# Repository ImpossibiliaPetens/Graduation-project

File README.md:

# Graduation-project

毕业设计项目的硬件资料与申报材料。

## 项目列表

| 目录 | 说明 | 状态 |
|---|---|---|
| [`hardware/stm32-environment-monitor`](hardware/stm32-environment-monitor) | **基于 STM32 的多功能环境智能监控系统**：温湿度、光照、RTC、OLED、按键、LED、蜂鸣器、12V 灯带控制，12V 输入板载降压 | V1.2，已提交嘉立创打样 |
| [`hardware/garden-watering-system`](hardware/garden-watering-system) | **智能花园浇水系统**：STM32F103C8T6 开发板 + BH1750 光照 + SHT30 温湿度 + 土壤湿度 + OLED + 4 按键，白天且土壤干才浇水（水泵/电磁阀用 LED 模拟），嘉立创 EDA 工程、Gerber、BOM、物资清单 | 硬件完成，已生成打板数据；程序待写 |
| [`hardware/parking-bluepill`](hardware/parking-bluepill) | **4 车位检测板**：Blue Pill 核心板 + 4 个红外反射传感器 + OLED（KiCad 工程） | `main` 为初版；**更新版在分支 [`claude/blissful-cannon-at318t`](../../tree/claude/blissful-cannon-at318t)**（尚未合并） |
| [`smart-agriculture`](smart-agriculture) | **禾智云枢：多模态 AI 视觉 + 农业智能体的智慧农业大棚沙盘**（800×400mm，STM32F4 + 4G/MQTT/OneNET）：创新创业训练计划申报书、问题—对策图、系统原理图、搭建工程蓝图、三维展示 | 方案设计阶段 |

## 环境监控板（V1.2）简介

- 主控：立创·地阔星 STM32F103C8T6 开发板，插在 2×20 排母上。
- 传感与显示：GXHT30C 温湿度、SD3077 实时时钟（CR1220 备份电池）、0.96" OLED（4P 母座）、光敏电阻。
- 输出：有源蜂鸣器、红/绿/黄 LED、12V LED 灯带（AO3400A 开关）。
- 输入：4 个按键（PA0~PA3）。
- 供电：12V DC 座 → 保险丝 → XL1509 降压到 5V；3.3V 由开发板 LDO 提供。
- 下载程序：开发板自带 SWD 口，接 DAP-Link；Type-C 只供电。

更多内容（引脚表、BOM、Gerber、装配注意事项）见
[环境监控板 README](hardware/stm32-environment-monitor/README.md)，
原理图见 [`docs/原理图.png`](hardware/stm32-environment-monitor/docs/原理图.png)。

## 车位检测板的更新版

更新版（2026-11-12）在分支 `claude/blissful-cannon-at318t`，`main` 上还是旧版。主要改动：

- 核心板改为 GD32F103C8T6 Type-C 核心板（引脚与 Blue Pill 兼容）。
- 传感器由 VCNT2030 改为 XL-ITR8307（成兴光，现货，引脚外露好焊）。
- 修正 OLED 引脚顺序，加去耦电容和 GND 铺铜，附嘉立创 SMT 的 BOM。
- PCB 文件改为 KiCad 9 格式，方便导入嘉立创 EDA。

详细说明见该分支的 `hardware/parking-bluepill/CHANGES.md`。

## 禾智云枢（智慧农业）简介

- 痛点：整体方案成本高、单点设备数据孤立、长势靠人工巡检、交互门槛高、AI 直控不安全、实训缺载体。
- 方案：STM32F4 + EC800K 4G/MQTT + OneNET 底座；AgriLeaf-Det / AgriGrow-Seg / AgriFusion / AgriAgent 四个 AI 模块；“建议—审批—执行”分级控制，断网时本地规则兜底。
- 材料：[申报书](smart-agriculture/项目申报书_公开版.docx)、[商业计划书](smart-agriculture/商业计划书.docx)；详见 [smart-agriculture/README.md](smart-agriculture/README.md)。

## 工具

- 环境监控板：嘉立创 EDA 专业版（`.epro`）
- 车位检测板：KiCad
- 智慧农业沙盘：STM32CubeMX、OneNET 云平台

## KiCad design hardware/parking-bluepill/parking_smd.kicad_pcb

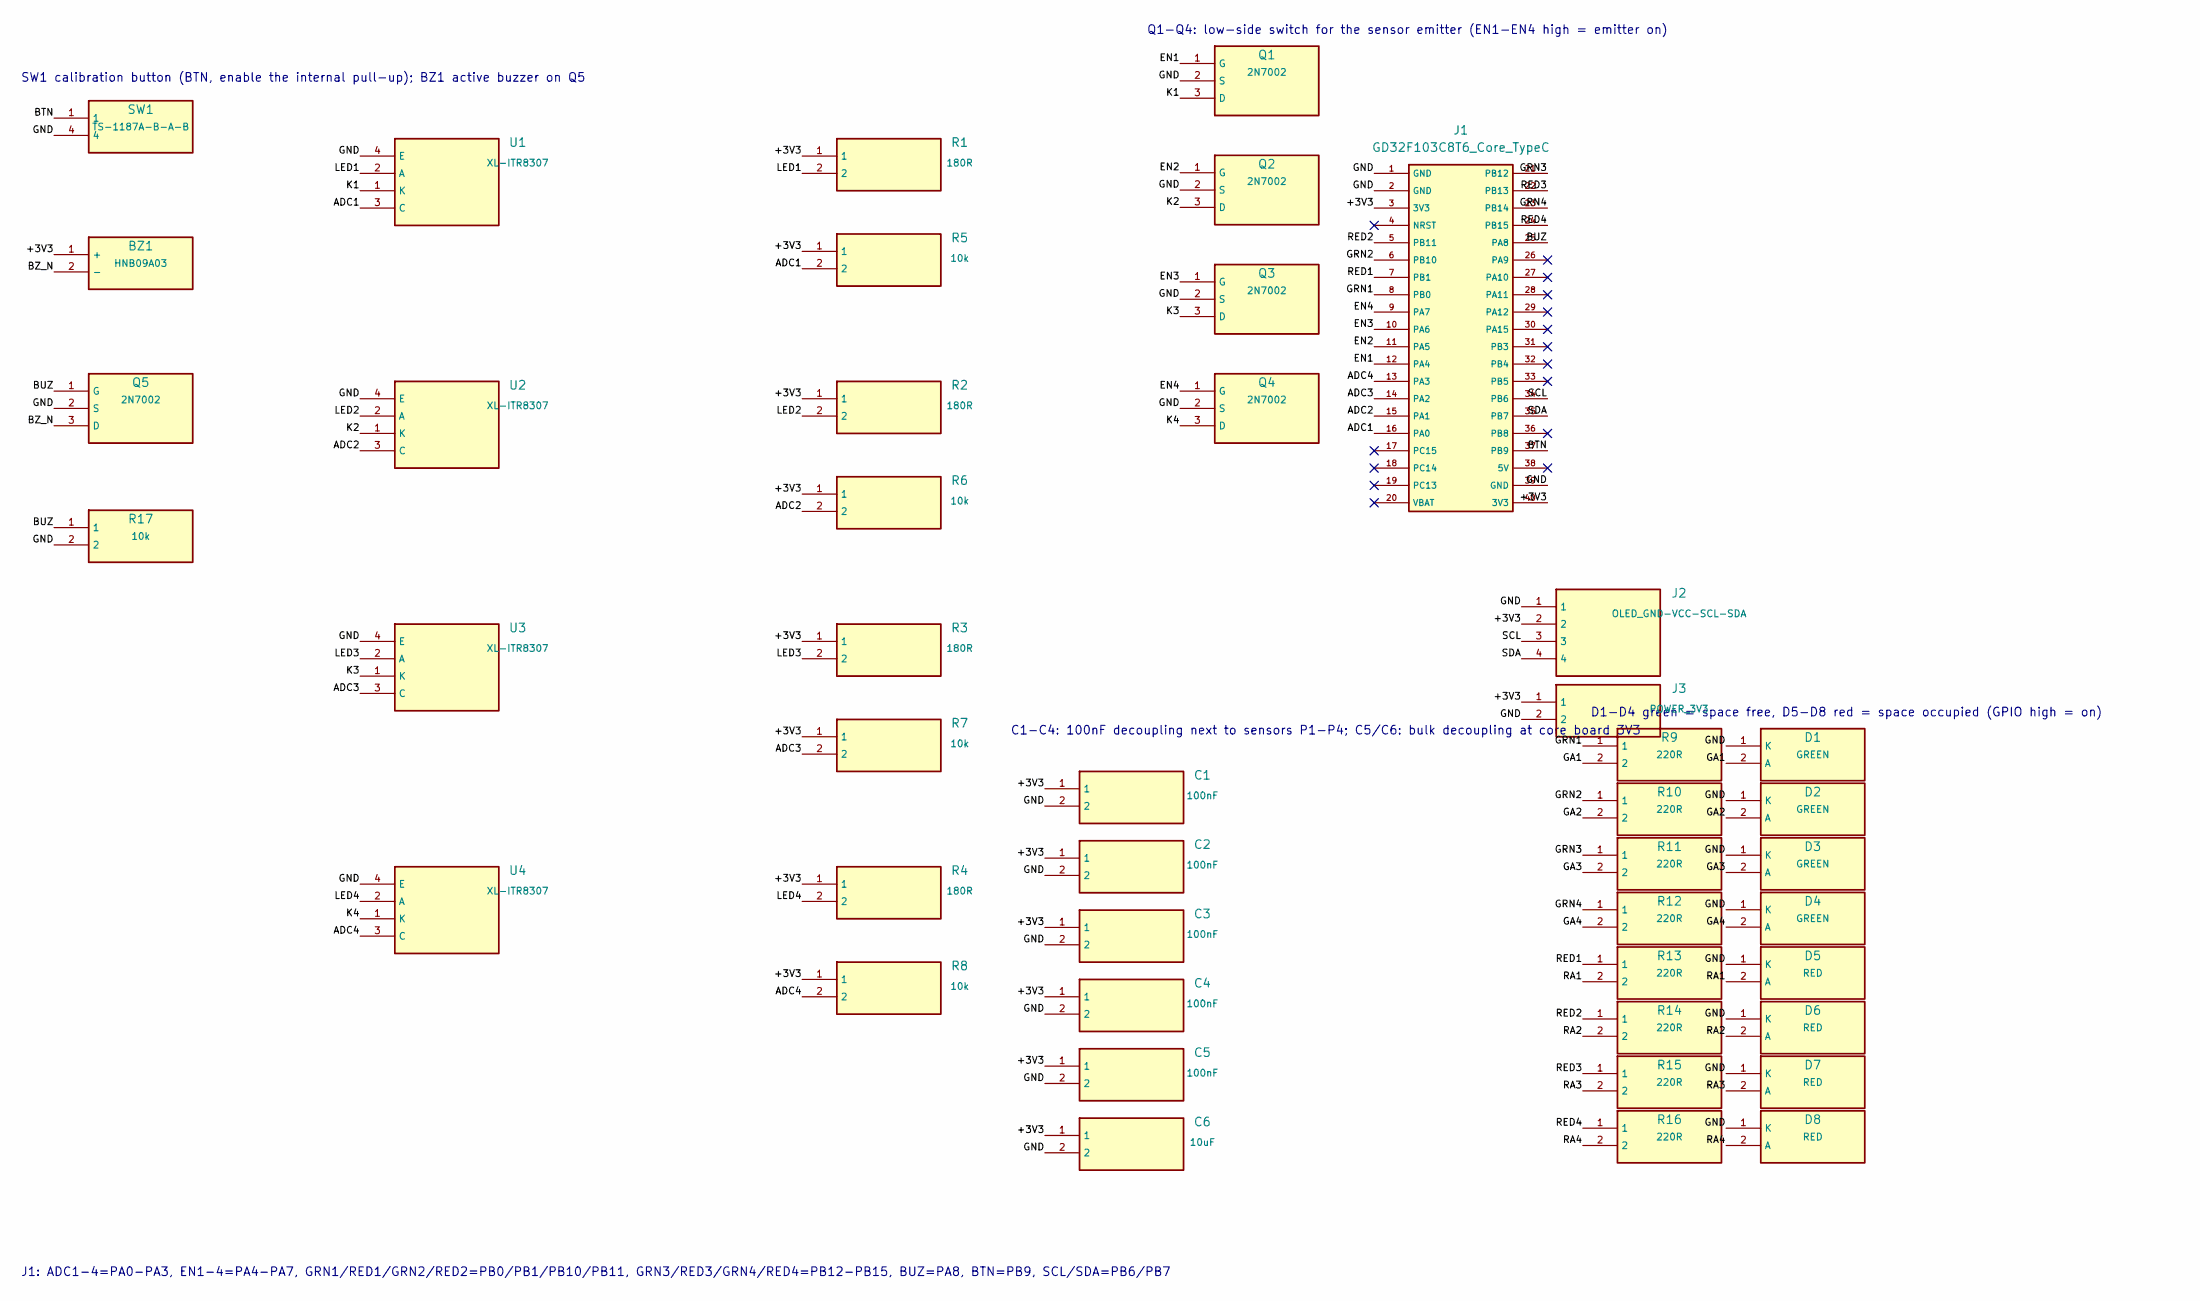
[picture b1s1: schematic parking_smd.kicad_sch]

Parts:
BZ1: HNB09A03; Buzzer_HNB09A03_D9_P5.0; LCSC C96102
C1, C2, C3, C4, C5: 100nF; C_0805_2012Metric; LCSC C49678
C6: 10uF; C_0805_2012Metric; LCSC C15850
D1, D2, D3, D4: GREEN; LED_0805_2012Metric; LCSC C84260
D5, D6, D7, D8: RED; LED_0805_2012Metric; LCSC C84256
J1: GD32F103C8T6_Core_TypeC; BluePill_2x20_P2.54_Row15.24
J2: OLED_GND-VCC-SCL-SDA; PinHeader_1x04_P2.54mm_Vertical
J3: POWER_3V3; PinHeader_1x02_P2.54mm_Vertical
Q1, Q2, Q3, Q4, Q5: 2N7002; SOT-23; LCSC C8545
R1, R2, R3, R4: 180R; R_0805_2012Metric; LCSC C25270
R5, R6, R7, R8, R17: 10k; R_0805_2012Metric; LCSC C17414
R9, R10, R11, R12, R13, R14, R15, R16: 220R; R_0805_2012Metric; LCSC C17557
SW1: TS-1187A-B-A-B; SW_TS1187A_5.1x5.1; LCSC C318884
U1, U2, U3, U4: XL-ITR8307; ITR8307; LCSC C7545642

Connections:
/+3V3: BZ1.1 (+), C1.1, C2.1, C3.1, C4.1, C5.1, C6.1, J1.3 (3V3), J1.40 (3V3), J2.2, J3.1, R1.1, R2.1, R3.1, R4.1, R5.1, R6.1, R7.1, R8.1
/ADC1: J1.16 (PA0), R5.2, U1.3 (C)
/ADC2: J1.15 (PA1), R6.2, U2.3 (C)
/ADC3: J1.14 (PA2), R7.2, U3.3 (C)
/ADC4: J1.13 (PA3), R8.2, U4.3 (C)
/BTN: J1.37 (PB9), SW1.1
/BUZ: J1.25 (PA8), Q5.1 (G), R17.1
/BZ_N: BZ1.2 (-), Q5.3 (D)
/EN1: J1.12 (PA4), Q1.1 (G)
/EN2: J1.11 (PA5), Q2.1 (G)
/EN3: J1.10 (PA6), Q3.1 (G)
/EN4: J1.9 (PA7), Q4.1 (G)
/GA1: D1.2 (A), R9.2
/GA2: D2.2 (A), R10.2
/GA3: D3.2 (A), R11.2
/GA4: D4.2 (A), R12.2
/GND: C1.2, C2.2, C3.2, C4.2, C5.2, C6.2, D1.1 (K), D2.1 (K), D3.1 (K), D4.1 (K), D5.1 (K), D6.1 (K), D7.1 (K), D8.1 (K), J1.1 (GND), J1.2 (GND), J1.39 (GND), J2.1, J3.2, Q1.2 (S), Q2.2 (S), Q3.2 (S), Q4.2 (S), Q5.2 (S), R17.2, SW1.4, U1.4 (E), U2.4 (E), U3.4 (E), U4.4 (E)
/GRN1: J1.8 (PB0), R9.1
/GRN2: J1.6 (PB10), R10.1
/GRN3: J1.21 (PB12), R11.1
/GRN4: J1.23 (PB14), R12.1
/K1: Q1.3 (D), U1.1 (K)
/K2: Q2.3 (D), U2.1 (K)
/K3: Q3.3 (D), U3.1 (K)
/K4: Q4.3 (D), U4.1 (K)
/LED1: R1.2, U1.2 (A)
/LED2: R2.2, U2.2 (A)
/LED3: R3.2, U3.2 (A)
/LED4: R4.2, U4.2 (A)
/RA1: D5.2 (A), R13.2
/RA2: D6.2 (A), R14.2
/RA3: D7.2 (A), R15.2
/RA4: D8.2 (A), R16.2
/RED1: J1.7 (PB1), R13.1
/RED2: J1.5 (PB11), R14.1
/RED3: J1.22 (PB13), R15.1
/RED4: J1.24 (PB15), R16.1
/SCL: J1.34 (PB6), J2.3
/SDA: J1.35 (PB7), J2.4

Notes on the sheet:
C1-C4: 100nF decoupling next to sensors P1-P4; C5/C6: bulk decoupling at core board 3V3
Q1-Q4: low-side switch for the sensor emitter (EN1-EN4 high = emitter on)
D1-D4 green = space free, D5-D8 red = space occupied (GPIO high = on)
SW1 calibration button (BTN, enable the internal pull-up); BZ1 active buzzer on Q5
J1: ADC1-4=PA0-PA3, EN1-4=PA4-PA7, GRN1/RED1/GRN2/RED2=PB0/PB1/PB10/PB11, GRN3/RED3/GRN4/RED4=PB12-PB15, BUZ=PA8, BTN=PB9, SCL/SDA=PB6/PB7

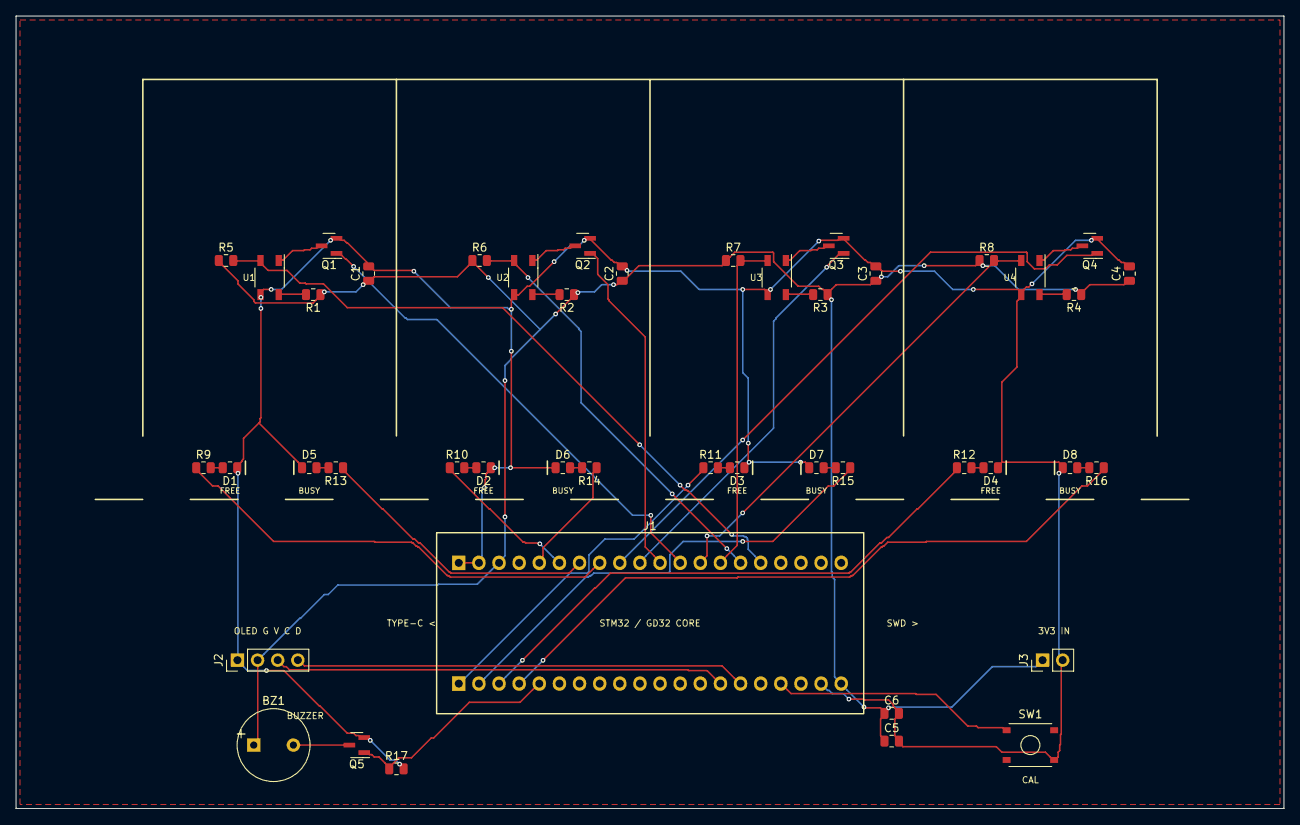
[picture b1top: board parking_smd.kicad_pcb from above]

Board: 2 copper layers, 160.0 x 100.0 mm, 45 parts (0 on the bottom side), 39 nets.

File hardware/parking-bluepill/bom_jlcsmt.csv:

Comment,Designator,Footprint,LCSC Part #
180R,"R1,R2,R3,R4",R_0805_2012Metric,C25270
10k,"R5,R6,R7,R8,R17",R_0805_2012Metric,C17414
220R,"R9,R10,R11,R12,R13,R14,R15,R16",R_0805_2012Metric,C17557
100nF,"C1,C2,C3,C4,C5",C_0805_2012Metric,C49678
10uF,C6,C_0805_2012Metric,C15850
XL-ITR8307,"U1,U2,U3,U4",ITR8307,C7545642
2N7002,"Q1,Q2,Q3,Q4,Q5",SOT-23,C8545
GREEN LED,"D1,D2,D3,D4",LED_0805_2012Metric,C84260
RED LED,"D5,D6,D7,D8",LED_0805_2012Metric,C84256
TS-1187A-B-A-B,SW1,SW_TS1187A_5.1x5.1,C318884
